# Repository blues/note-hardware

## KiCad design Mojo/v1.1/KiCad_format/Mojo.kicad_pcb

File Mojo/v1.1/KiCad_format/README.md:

# Mojo v1.1 — KiCad format

This directory contains the design files for the Blues **Mojo** v1.1
(internal design name *Mojo-v4*) in **KiCad 9** format. They were generated
by porting the original Altium Designer design files found in
[`../Sources/`](../Sources/), and validated against the shipped BOM and
fabrication outputs — see
[`documentation/Porting-Notes.md`](documentation/Porting-Notes.md) for the
full porting log and [`validation/`](validation/) for the evidence
(ERC/DRC reports, per-layer gerber diffs against the production gerbers,
KiCanvas render checks).

## Contents

| Path | Description |
|---|---|
| `Mojo.kicad_pro` / `Mojo.kicad_prl` | KiCad project (design rules match the Altium DRC report) |
| `Mojo.kicad_sch` | Schematic (single flat sheet, symbols embedded) |
| `Mojo.kicad_pcb` | Board (footprints embedded; zone fills preserved from the Altium import — do not refill) |
| `Mojo.kicad_wks` | Drawing sheet (shared Blues template) |
| `Mojo-altium-import.kicad_sym` / `Mojo-altium-import.pretty/` | Project symbol/footprint libraries captured during the import |
| `sym-lib-table` / `fp-lib-table` | Library tables (project libraries + optional [blues-kicad-lib]) |
| `documentation/` | Porting notes and plotted schematic/board PDFs |
| `manufacturing/Mojo_RevA.zip` | Gerbers + Excellon drill files exported from KiCad (the authoritative production package remains [`../Fabrication/`](../Fabrication/)) |
| `validation/` | Port-QA artifacts: ERC/DRC reports, `<Layer>-{KiCad,Altium,diff}.png` gerber diffs, BOM comparison, KiCanvas screenshots |

The project is self-contained: all symbols and footprints are embedded or
provided in the project libraries. The external [blues-kicad-lib] is only
referenced for consistency with the other Blues KiCad ports and is not
required to open or edit this project. No 3D models are included.

Note: the production ("Normal") assembly variant is represented with KiCad
DNP flags on J2/J3/J7/J8; test point, mounting holes and logo items are
excluded from the BOM, matching the shipped
[`BOM-Mojo-v4-Normal.xls`](../Assembly%20Normal/BOM/).

## Revision History

| Revision | Date | Author | Notes |
|---|---|---|---|
| A | 2026-07-28 | Blues Inc | Initial port of Mojo v1.1 (Mojo-v4) from Altium Designer sources, KiCad 9.0.9 |

### Original (Altium) revision

| Revision | Notes |
|---|---|
| v4 (public v1.1) | Production release, 2024-06 |

[blues-kicad-lib]: https://github.com/blues/blues-kicad-lib

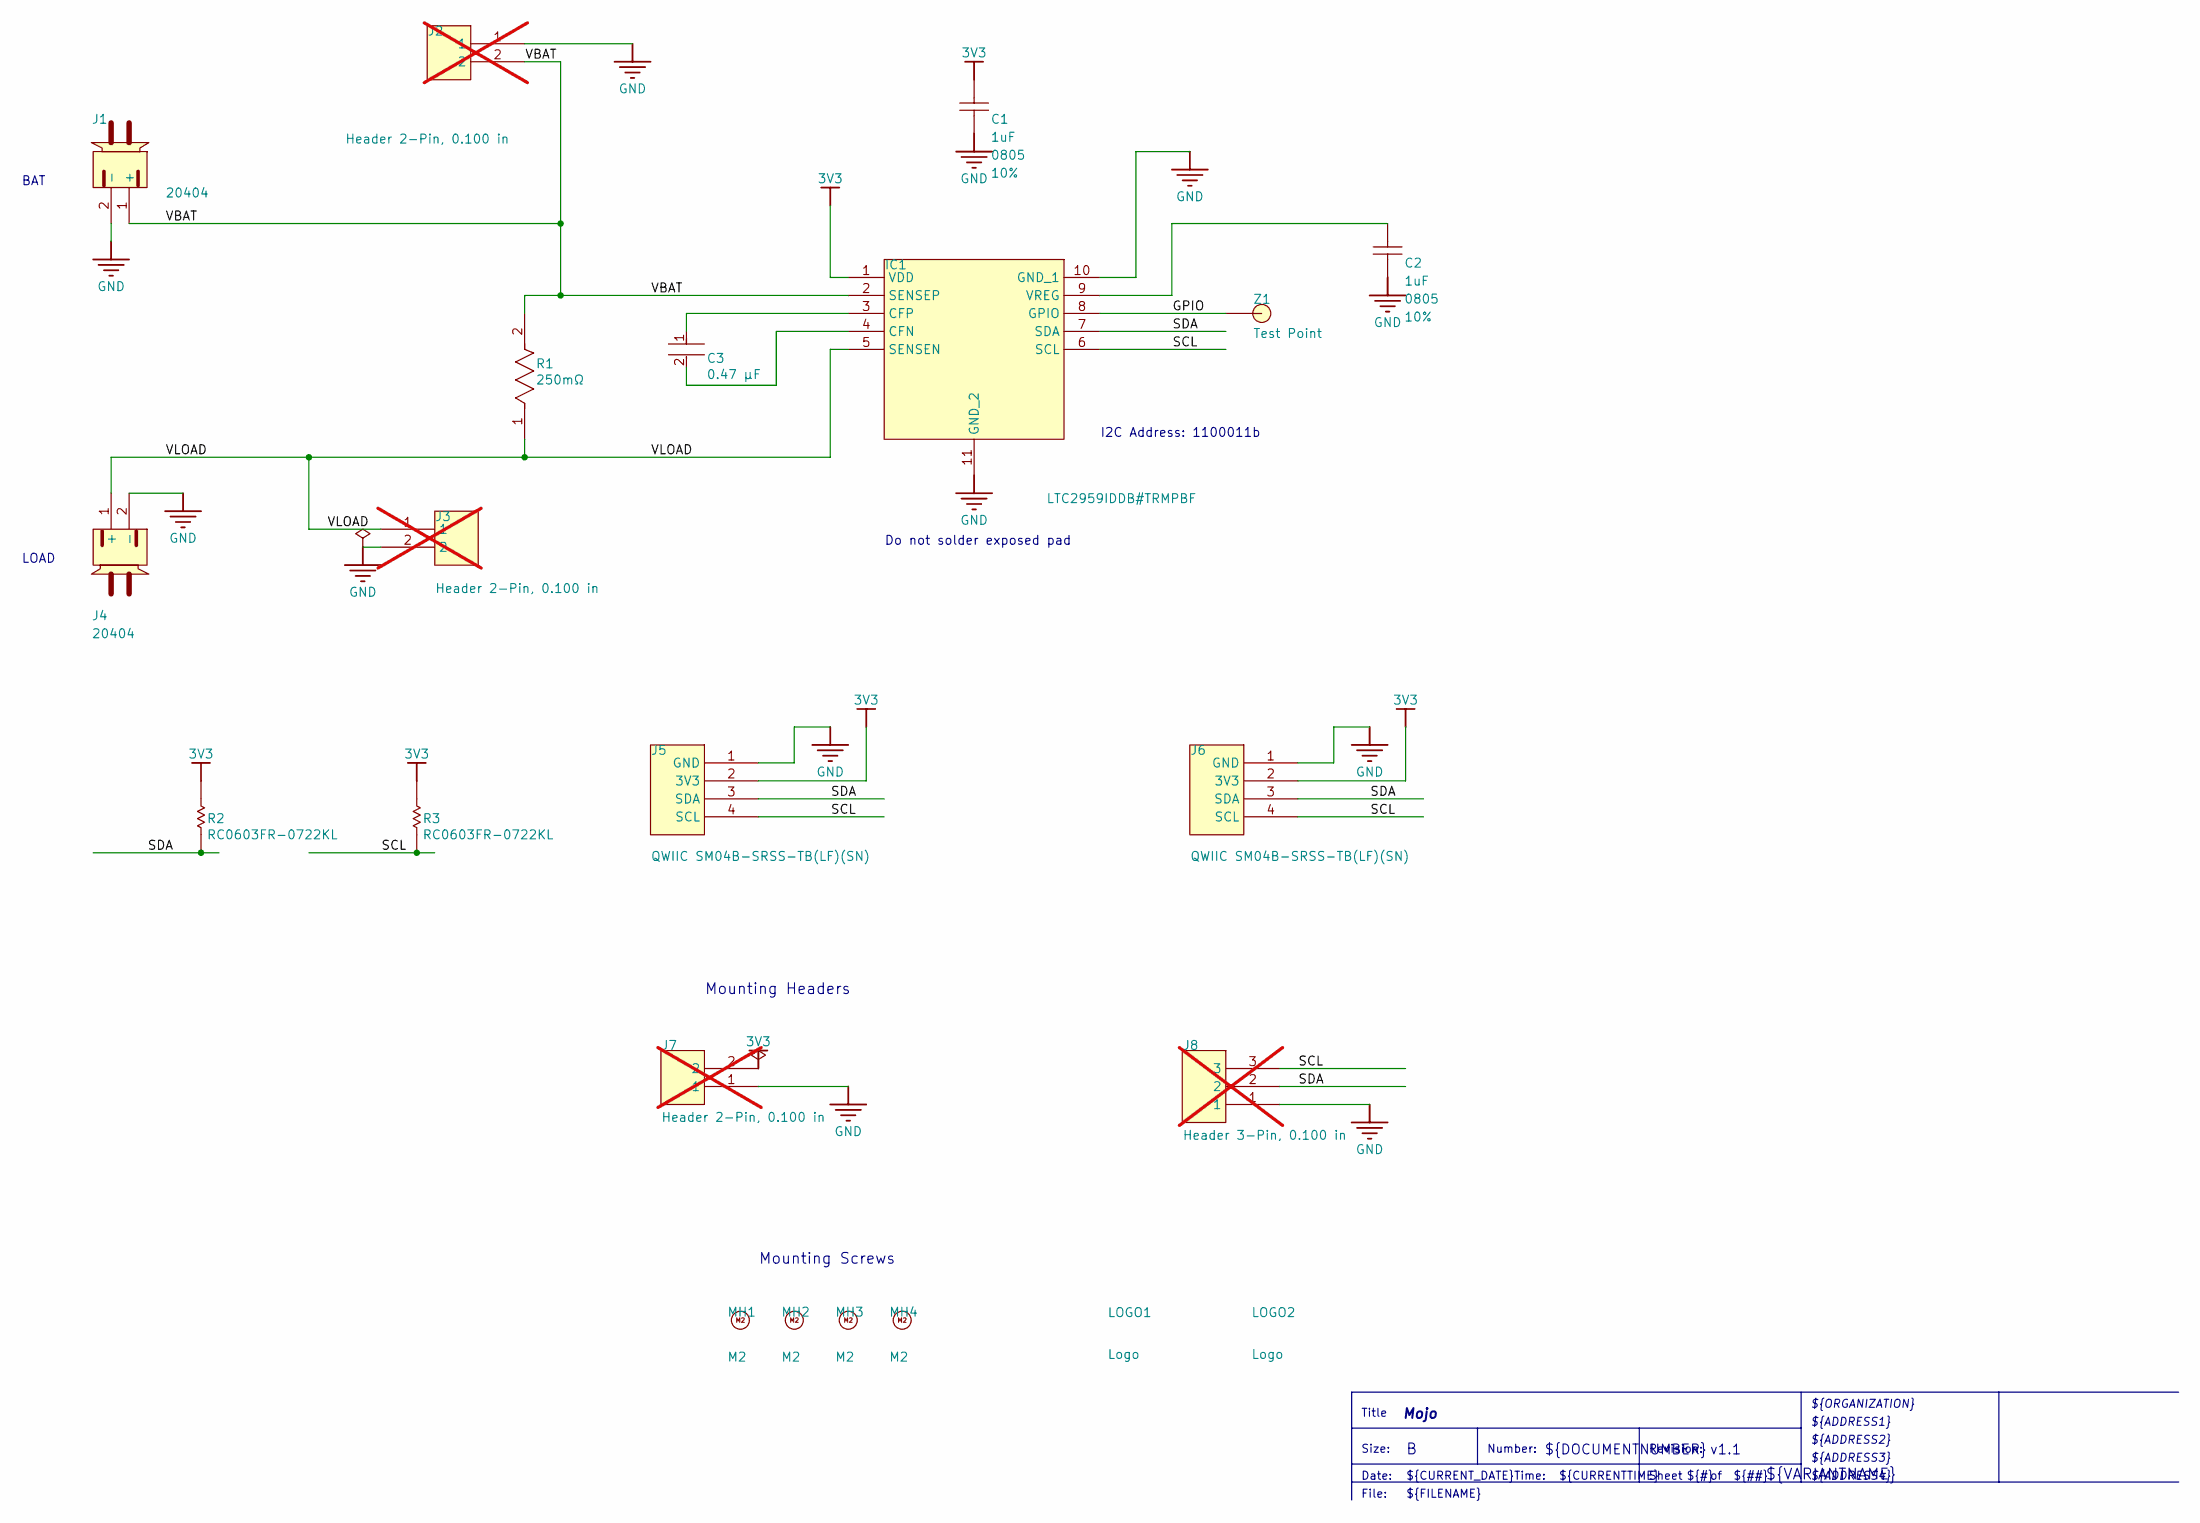
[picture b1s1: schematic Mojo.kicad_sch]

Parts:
C1, C2: GRM216R61E105KA12D; CAPC2013X70X45NL10T25; VOLTAGE 25V; TOLERANCE 10%; PART NUMBER GRM216R61E105KA12D
C3: C0805C474K5RACTU; FP-C0805C-DN-MFG; VOLTAGE RATING 50 V; TOLERANCE 0.1; MANUFACTURER PART NUMBER C0805C474K5RACTU; DIGIKEY DESCRIPTION CAP CER 0.47UF 50V 10% X7R 0805
IC1: LTC2959IDDB#TRMPBF; SON50P200X300X80-11N-D; MANUFACTURER_PART_NUMBER LTC2959IDDB#TRMPBF; MOUSER PART NUMBER 584-LTC2959IDDBTRMPB
J1, J4: 20404; BAT-AF-S2B-PH-SM4; MANUFACTURER PART NUMBER 20404
J2, J3, J7: Header 2-Pin, 0.100 in; HEADER_AA_002; MANUFACTURER PART NUMBER PEC02SAAN; not fitted
J5, J6: QWIIC SM04B-SRSS-TB(LF)(SN); QWIIC_SM04B-SRSS; MAX VOLTAGE RATING (AC) 50V; MAX VOLTAGE RATING (DC) 50V; MANUFACTURER PART NUMBER SM04B-SRSS-TB(LF)(SN)
J8: Header 3-Pin, 0.100 in; HEADER_AA_003; MANUFACTURER PART NUMBER PEC03SAAN; not fitted
LOGO1, LOGO2: Logo
MH1, MH2, MH3, MH4: M2; HOLE_2MM
R1: WSL2010R2500FEA; FP-WSL2010-0_508-MFG; VOLTAGE RATING (DC) 150mV; VOLTAGE RATING (AC) 150mV; MANUFACTURER PART NUMBER WSL2010R2500FEA
R2, R3: RC0603FR-0722KL; RESC1608X55X25LL10T15; TOLERANCE 10%; CURRENT RATING 290 mA
Z1: Test Point; testp_40pad

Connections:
3V3: C1.2, IC1.1 (VDD), J5.2 (3V3), J6.2 (3V3), J7.2, R2.2, R3.2
/GPIO: IC1.8 (GPIO), Z1.1
/SCL: IC1.6 (SCL), J5.4 (SCL), J6.4 (SCL), J8.3, R3.1
/SDA: IC1.7 (SDA), J5.3 (SDA), J6.3 (SDA), J8.2, R2.1
/VBAT: IC1.2 (SENSEP), J1.1 (+), J2.2, R1.2
/VLOAD: IC1.5 (SENSEN), J3.1, J4.1 (+), R1.1
GND: C1.1, C2.1, IC1.10 (GND_1), IC1.11 (GND_2), J1.2 (-), J2.1, J3.2, J4.2 (-), J5.1 (GND), J6.1 (GND), J7.1, J8.1
unnamed: C3.2, IC1.4 (CFN)
unnamed: C3.1, IC1.3 (CFP)
unnamed: C2.2, IC1.9 (VREG)

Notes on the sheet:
I2C Address: 1100011b
Number:
Size:
${CURRENTTIME}
${CURRENT_DATE}
Date:
${#}
${ADDRESS3}
${REVISION}
LOAD
File:
Revision:
BAT
${TITLE}
Mounting Screws
${ADDRESS2}
${VARIANTNAME}
Time:
${##}
Mounting Headers
${ADDRESS1}
Do not solder exposed pad
Title
${DOCUMENTNUMBER}
${ORGANIZATION}
${FILENAME}
${ADDRESS4}
Sheet

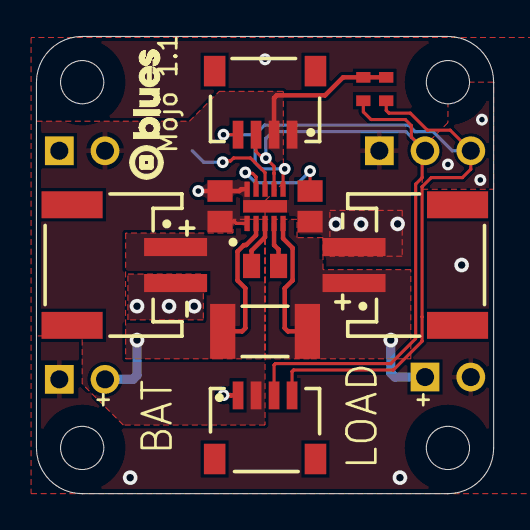
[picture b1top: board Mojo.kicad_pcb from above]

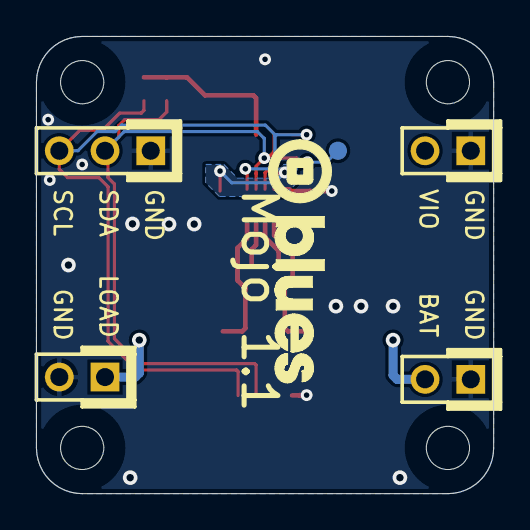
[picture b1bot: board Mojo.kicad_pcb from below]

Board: 2 copper layers, 25.4 x 25.4 mm, 20 parts (5 on the bottom side), 10 nets.

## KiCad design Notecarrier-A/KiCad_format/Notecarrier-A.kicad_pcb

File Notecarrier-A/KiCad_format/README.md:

# Notecarrier-A

This folder contains the design files for the Blues Wireless Notcarrier-A, in KiCad 7 format. They were generated by porting the original OrCad design files. For a detailed description of the porting process, see [PortingNotes](documentation/PortingNotes.md).

**Note:** re-filling zones will result in differences to the `F.Cu` layer. To mimic the unusual clearance near `U5`, the track at (62.9, 109.5) must first be cut to the clipboard, then the zones refilled and then the track pasted back into place. The details are in [PortingNotes](documentation/PortingNotes.md).

Components in this design are sourced from the [blues-kicad-lib](https://github.com/blues/blues-kicad-lib) library. However, with the exception of 3D models, KiCad produces self-contained project files. Thus this project can still be used without access to the library.

## Contents

- This file
 	- `README.md`
- KiCad source files
	- `Notecarrier-A.kicad_dru`
	- `Notecarrier-A.kicad_pcb`	- `Notecarrier-A.kicad_prl`	- `Notecarrier-A.kicad_pro`	- `Notecarrier-A.kicad_sch`	- `Notecarrier-A.kicad_wks`
	- `sym-lib-table`
	- `fp-info-cache`	- `fp-lib-table`
- Documentation	- `documentation/*`
- Manufacturing artefacts
	- `manufacturing/*`
- Design references
	- `reference/*`
- Validation artefacts
	- `validation/*`

## Revision History

| Revision |    Date    |   Author   | Description |
|:--------:| ---------- | ---------- | ----------- |
|     A    | 2023-05-23 | H.Raftery  | Initial port from OrCAD design files, rev 16 (v2.0). |

### Original OrCAD Design File Revision History

| Revision |    Date    |   Author   | Description |
|:--------:| ---------- | ---------- | ----------- |
|    16    | 01/10/2021 | G.Boschini | - Added QWIIC connectors |

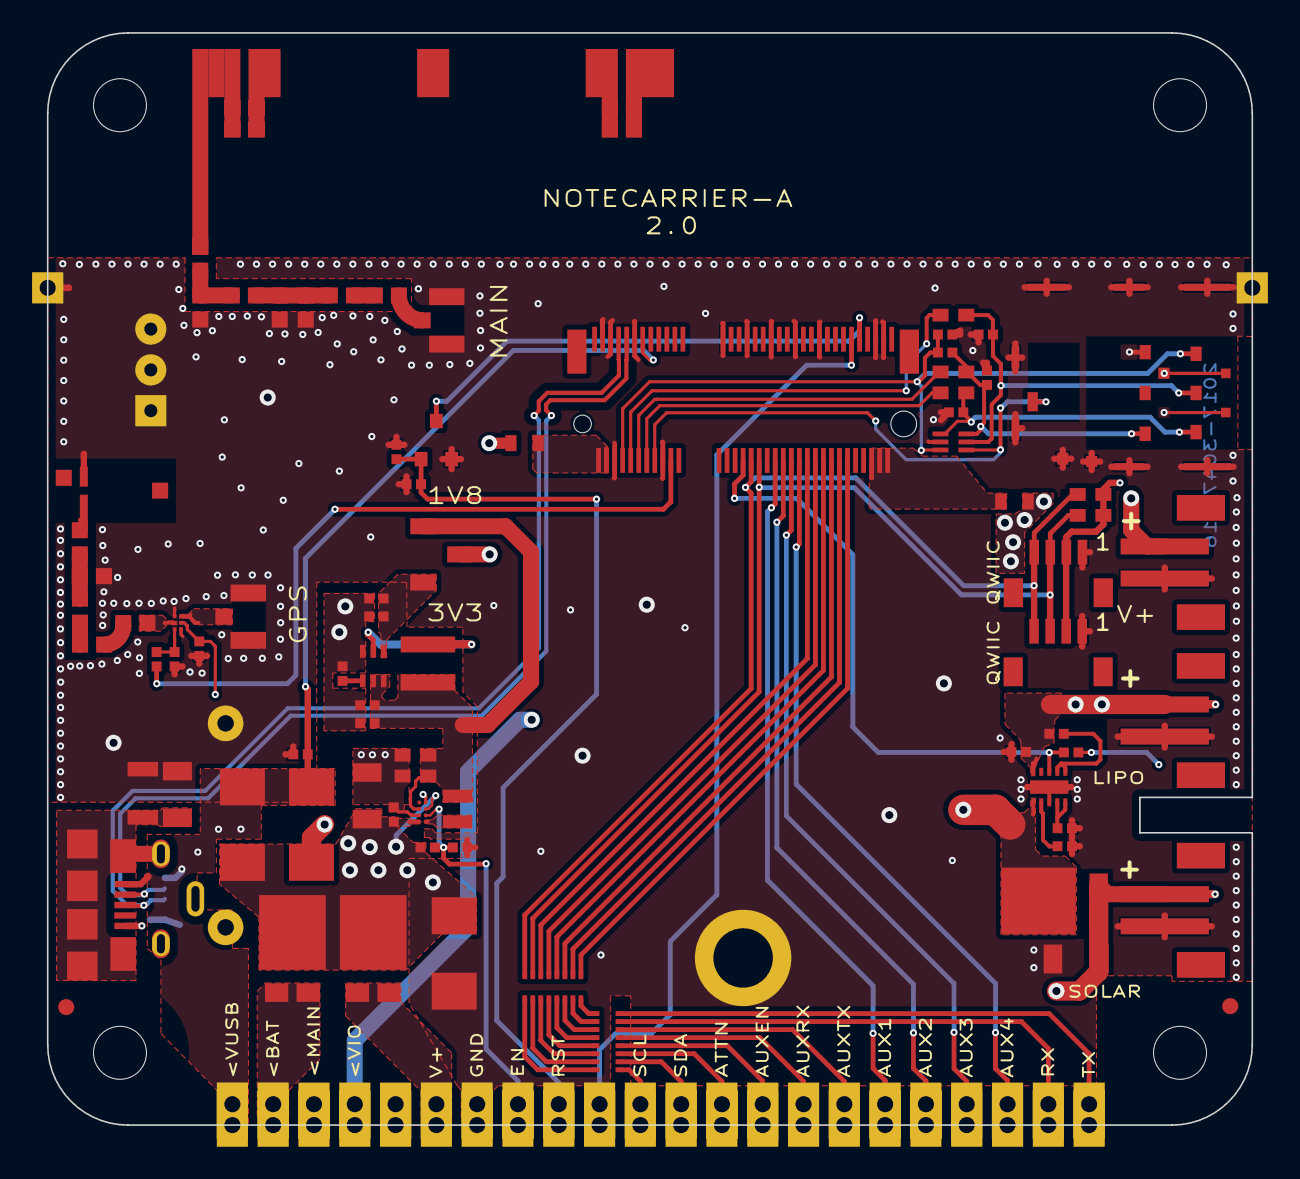
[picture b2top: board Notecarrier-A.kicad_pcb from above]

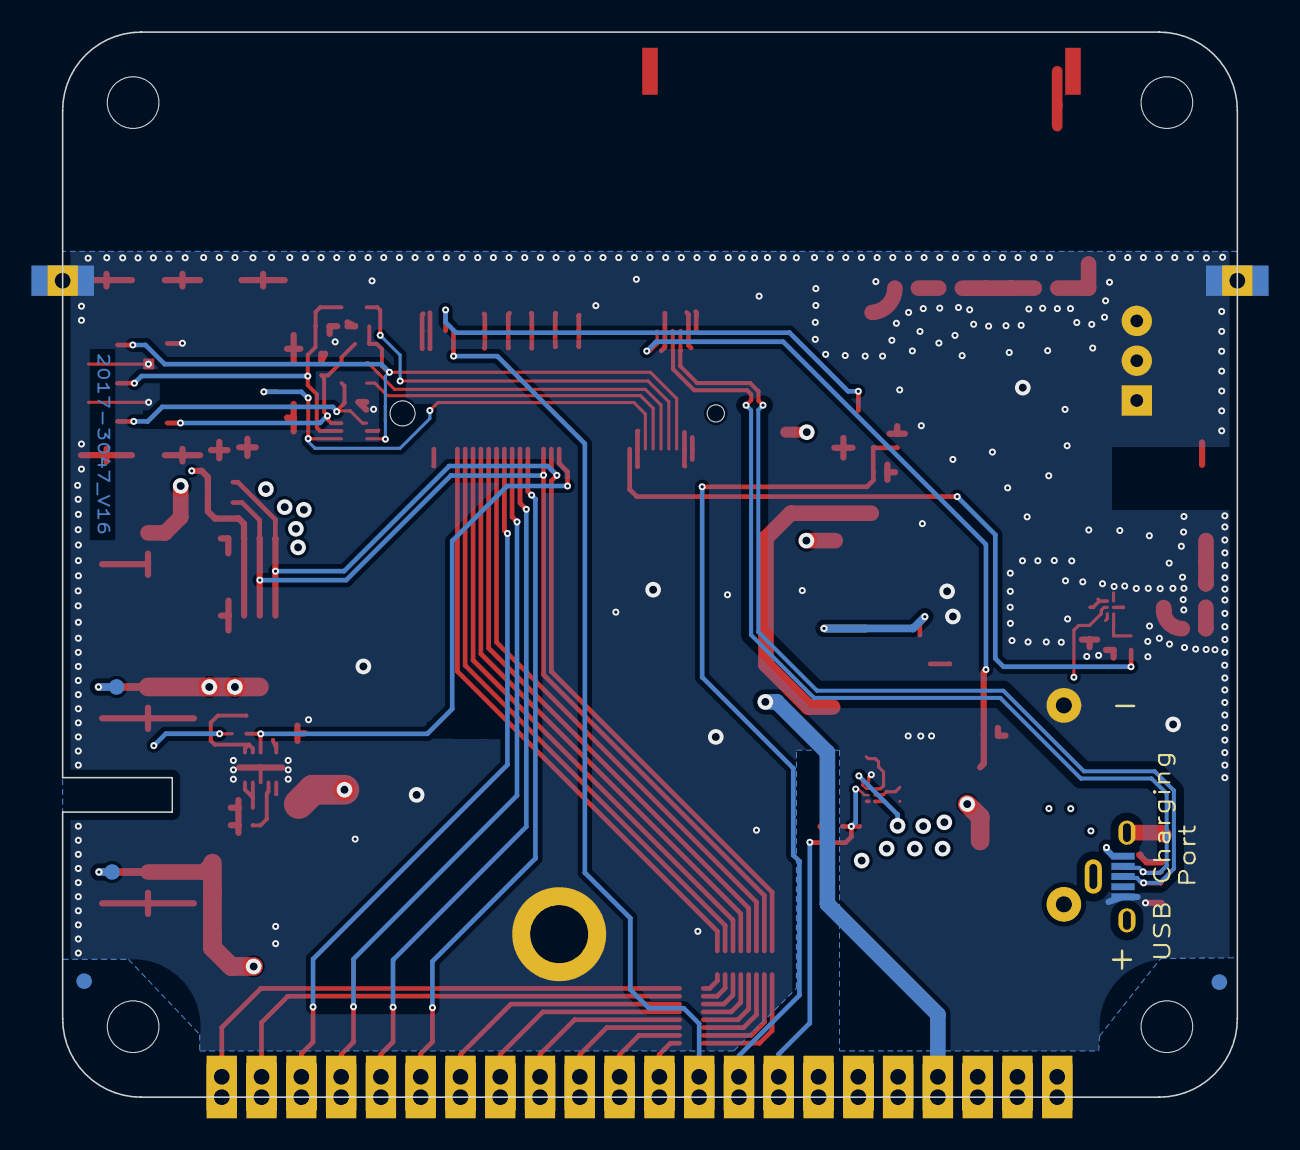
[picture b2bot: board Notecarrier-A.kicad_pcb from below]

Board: 4 copper layers, 75.0 x 68.0 mm, 99 parts (6 on the bottom side), 79 nets.

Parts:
ANT1: NN03-310; ANT-NN03310-LTE_NO-SILK
ANT2: NN03-320; ANT-NN03320-GPS_NO-SILK
BAT1: NU; BATHLD-2464-NO_MECH
C1: 47u/16V-X5R; CS-C-1206
C2: 4.7u/6.3V-X5R; CS-C-0402
C3, C4: 10u/10V-X5R; CS-C-0603
C5, C6, C9, C10, C16, C23: 100n/16V; CS-C-0402
C7, C8: 10u/6.3V-X5R; CS-C-0402
C11: 10n/1kV; CS-C-1206
C12: 10u/25V-X5R; CS-C-1206
C13, C22: 1u/16V-X5R; CS-C-0402
C17, C18, C19: 33p/50V-C0G; CS-C-0402
C21: 1n/50V; FRACTUS-0404_NO-SILK
C25: 0.5p/50V-C0G; FRACTUS-0404_NO-SILK
C26: 1p/50V-C0G; FRACTUS-0404_NO-SILK
C27: 2.2p/50V-C0G; FRACTUS-0404_NO-SILK
C28: 4.6p/50V-C0G; FRACTUS-0404_NO-SILK
C29: 1.1p/50V-C0G; FRACTUS-0404_NO-SILK
DS2, DS3, DS6: FSV1045V; TO277-3
DS4, DS5: STPS3H100U; SMB
F1: SF-0603F150-2; FS-0603
F2: 3.5A/32V; FS-0603
FID1, FID2, FID3, FID4: TPS; FIDUCIAL_MIN-CLEARANCE
H1, H2, H3, H4: MountingHole; FORO-0330-U
J2: NU; J-5-0065-FDS-UUSB1051330001_NO-SILK
J3, J4, J12: B2B-PH-SM4-TBT(LF)(SN); J-2-0200-MDS-B2B-PH-SM4
J5: NanoSIM - SF72S006VBAR2500; J-NANOSIM-SF72S006VBA_NO-FILL
J6: MDT420E01001; J-75-0050-MOS-M2-E_smaller-mask
J7, J8: uFL-R-SMT-1-10; J-3-MDS-UFL_NO-SILK
J9: 12734; J-22-0254-FDT-H0508_EDGE
J10: 00711; J-3-0254-FDT_H0508
J11: 10118192-0002LF; J-5-0065-FOS-USB10118192-NOF
J13, J14: BM04B-SRSS-TBT; J-4-0100-MDS-SH_NO-SILK
L1: XFL4020-222MEC; LS-XFL4020
L2: 1285AS-H-2R2M=P2; LS-0806
L5: LQW15AN7N5H00D; FRACTUS-0404_NO-SILK
L6: LQW18AN12NG80; FRACTUS-0404_NO-SILK
L7: LQW18AN10NG80D; FRACTUS-0404_NO-SILK
L8: LQW18AN8N4G80D; FRACTUS-0404_NO-SILK
L9: LQW15AN2N3G80D; FRACTUS-0404_NO-SILK
OBJ1: 9774025151R; DIST-WASMSIM0250
PAD1, PAD2: TPS; PAD-THT-CAS-0100
Q1: AO3420; SOT23
R1: 10M/5%; RS-0402
R4: 82k; RS-0402
R5: 1M; RS-1206
R6: NU; RS-0402
R8, R10: 10k; RS-0402
R9: 470R; RS-0402
R12, R14, R15: 22R; RS-0603
R16: 15k; RS-0402
R18: 200k; RS-0402
R21: 1k; RS-0402
R22: 100k; RS-0402
R25, R27, R28, R29: 0R; FRACTUS-0404_NO-SILK
R26: NU; FRACTUS-0404_NO-SILK
R30, R31: NU; RS-0603
RR1, RR2: 100R/5%; RR-8X-1506
SW1: CJS-1200TA; SW_CJS-1200TA_NO-SILK
TP4, TP5: TPS; TPS-SPEA
TVS1: SM6T6V8A; SMB
TVS2: ESDLC5V0M5-TP; SOT666_NO-SILK
U1: TPS62748YFPT; XFBGA8
U2: MAX17225ELT; WDFN6-0200X0200
U3: BQ24210DQCT; WSON10-EXP_NO-SILK
U5: BGA725L6E6327FTSA1; XFDFN6_NO-SILK

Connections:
+1V8: C3.1, C4.1, C8.1, C9.1, L1.2, L2.2, SW1.1 (C), U1.C2 (VOS), U2.5 (IN), U2.6 (EN)
+3V3: C6.1, C7.1, SW1.3 (A), U2.1 (OUT)
/Connector/ATTN_P: J6.54 (ATTN_P), RR2.14 (R3_2)
/Connector/AUX_EN_P: J6.56 (AUX_EN_P), RR2.13 (R4_2)
/Connector/AUX_RX_P: J6.58 (AUX_RX_P), RR2.12 (R5_2)
/Connector/AUX_TX_P: J6.60 (AUX_TX_P), RR2.11 (R6_2)
/Connector/GPS_50: J8.1 (In), U5.3 (AO)
/Connector/GPS_50_A: L5.1, U5.5 (AI)
/Connector/GPS_50_B: C21.1, L5.2
/Connector/GPS_50_C: C21.2, R29.1
/Connector/GPS_50_D: C28.1, C29.1, R29.2
/Connector/GPS_50_E: ANT2.4 (FEED-GPS), C29.2
/Connector/LTE_50: J7.1 (In), R28.1
/Connector/LTE_50_A: R27.1, R28.2
/Connector/LTE_50_B: C26.1, C27.2, L7.1, R27.2
/Connector/LTE_50_C: C27.1, L8.1, L9.1
/Connector/LTE_50_D: ANT1.1 (FEED_LTE), L9.2
/Connector/NRST: J6.67 (NRST), Q1.3 (D)
/Connector/RX_P: J6.62 (RX_P), RR2.10 (R7_2)
/Connector/SCL_P: J6.40 (SCL_P), J13.4, J14.4, R31.1, RR2.16 (R1_2)
/Connector/SDA_P: J6.42 (SDA_P), J13.3, J14.3, R30.1, RR2.15 (R2_2)
/Connector/SIM_CLK: J6.14 (SIM_CLK), R14.1
/Connector/SIM_IO: J6.12 (SIM_IO), R12.1
/Connector/SIM_NPRESENT: J5.DSW, J6.16 (SIM_NPRESENT), TVS2.4 (K3)
/Connector/SIM_RST: J6.10 (SIM_RST), R15.1
/Connector/SIM_VCC: C16.1, J5.C1 (VCC), J6.8 (SIM_VCC), R16.2, TVS2.3 (K2)
/Connector/TX_P: J6.64 (TX_P), RR2.9 (R8_2)
/Power/EN: C5.1, J9.8, R1.1, U1.B1 (EN)
ATTN: J9.13, RR1.3 (R3_1)
AUX1: J6.46 (AUX1), J9.17
AUX2: J6.48 (AUX2), J9.18
AUX3: J6.50 (AUX3), J9.19
AUX4: J6.52 (AUX4), J9.20
AUX5: J6.38 (NC38), R6.1, U3.8 (~CHG)
AUX_EN: J9.14, RR1.4 (R4_1)
AUX_RX: J9.15, RR1.5 (R5_1)
AUX_TX: J9.16, RR1.6 (R6_1)
BOOT: J6.65 (NC65), J9.10
GND: ANT2.2 (M2), BAT1.2 (-), C1.2, C2.2, C3.2, C4.2, C5.2, C6.2, C7.2, C8.2, C9.2, C10.2, C11.2, C12.2, C13.2, C16.2, C17.2, C18.2, C19.2, C22.2, C23.2, C26.2, C28.2, J2.5 (GND), J3.2, J4.2, J5.C5 (GND), J5.CSW, J5.SH, J6.3 (GND), J6.5 (GND), J6.6 (GND), J6.11 (GND), J6.18 (GND), J6.33 (GND), J6.39 (GND), J6.45 (GND), J6.51 (GND), J6.57 (GND), J6.71 (GND), J6.73 (GND), J7.2 (Ext), J8.2 (Ext), J9.7, J10.1, J10.2, J10.3, J11.5 (GND), J12.2, J13.1, J14.1, L7.2, L8.2, OBJ1.1, PAD1.1, PAD2.1, Q1.2 (S), R4.1, R5.2, R9.1, R10.1, R21.1, R22.1, TVS1.2 (A2), TVS2.2 (A), U1.B2 (GND), U1.D1 (CTRL), U2.3 (GND), U3.3 (VSS), U3.11 (EXP), U5.1 (GND), U5.4 (GNDRF)
unnamed: DS5.1 (K), DS6.3 (C), U3.1 (VBUS)
unnamed: C11.1, J2.6 (Shield), J11.6 (Shield), R5.1
unnamed: ANT1.2 (MN1-A), C25.2, L6.1
unnamed: ANT1.3 (MN1-B), C25.1, L6.2
unnamed: ANT1.5 (MN2-A), R25.1, R26.1
unnamed: ANT1.6 (MN2-B), R25.2, R26.2
unnamed: C18.1, J5.C3 (CLK), R14.2, TVS2.1 (K1)
unnamed: C19.1, J5.C7 (I/O), R12.2, R16.1, TVS2.6 (K5)
unnamed: C17.1, J5.C2 (RST), R15.2, TVS2.5 (K4)
unnamed: RR1.16 (R1_2), RR2.1 (R1_1)
unnamed: RR1.15 (R2_2), RR2.2 (R2_1)
unnamed: RR1.14 (R3_2), RR2.3 (R3_1)
unnamed: RR1.13 (R4_2), RR2.4 (R4_1)
unnamed: RR1.12 (R5_2), RR2.5 (R5_1)
unnamed: RR1.11 (R6_2), RR2.6 (R6_1)
unnamed: RR1.10 (R7_2), RR2.7 (R7_1)
unnamed: RR1.9 (R8_2), RR2.8 (R8_1)
unnamed: L2.1, U1.A1 (SW)
unnamed: L1.1, U2.2 (LX)
unnamed: R4.2, U2.4 (SEL)
unnamed: R9.2, U3.2 (ISET)
unnamed: R10.2, U3.4 (VTSB), U3.5 (TS)
unnamed: R8.1, U3.6 (~PG), U3.7 (~EN)
unnamed: R18.1, R22.2, U5.6 (PON)
RST: C23.1, J9.9, Q1.1 (G), R21.2
RX: J9.21, RR1.7 (R7_1)
SCL: J9.11, RR1.1 (R1_1)
SDA: J9.12, RR1.2 (R2_1)
TX: J9.22, RR1.8 (R8_1)
USB_DM: J2.2 (D-), J6.9 (USB_DM), J11.2 (D-)
USB_DP: J2.3 (D+), J6.7 (USB_DP), J11.3 (D+)
V+: DS2.1 (A1), DS2.2 (A2), J9.6, J12.1
VACT_GPS_OUT: J6.20 (VACT_GPS_OUT), R18.2
VBAT: BAT1.1 (+), C13.1, DS3.1 (A1), DS3.2 (A2), J4.1, J9.2, R8.2, TP4.1, U3.10 (BAT)
VIO: C22.1, F1.1, J9.4, J13.2, J14.2, R6.2, R30.2, R31.2, SW1.2 (B), U5.2 (VCC)
VIO_P: F1.2, J6.2 (VIO_P), J6.4 (VIO_P)
VMAIN: C1.1, C2.1, DS2.3 (C), DS3.3 (C), DS4.1 (K), F2.1, J9.3, R1.2, TVS1.1 (A1), U1.A2 (VIN), U1.C1 (VSEL)
VMODEM_P: F2.2, J6.70 (VMODEM_P), J6.72 (VMODEM_P), J6.74 (VMODEM_P)
VSOLAR: C12.1, DS6.1 (A1), DS6.2 (A2), J3.1, J9.5, TP5.1
VUSB: C10.1, DS4.2 (A), DS5.2 (A), J2.1 (VBUS), J6.13 (VUSB), J9.1, J11.1 (VBUS)

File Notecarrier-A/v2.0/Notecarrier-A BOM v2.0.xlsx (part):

PROJECT |  | 2017-3047 (NOTECARRIER-M2-AL) |  | Blues Inc
REVISION |  | 16
SCHEMATIC |  | 20173047_NOTECARRIER-M2-AL_V16
DATE |  | 15/11/2021
Item | Quantity | Reference | Part | MPN | Description | Temperature | Type | Package
1 | 1 | ANT1 | NN03-310 | NN03-310 | ANTENNA CHIP LTE/GNSS/BT D=30X3X1 NN03-310 IGNION SMT | -40°..+125° | SMD | ANT-NN03310-LTE
2 | 1 | ANT2 | NN03-320 | NN03-320 | ANTENNA CHIP GPS/BT D=3X7X2 NN03-320 IGNION SMT | -40°..+85° | SMD | ANT-NN03320-GPS
3 | 1 | CS1 | CS V16 4L 35um |  | C.S. NOTECARRIER-M2-AX V16 (75X65)mm 4L/SO/SR ENIG TG150 sp=1.6mm Cu=35um (CONT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 | TG150
4 | 1 | C1 | 47u/16V-X5R | C3216X5R1E476M160AC | CHIP CAP.CER. 47uF 16V 20% X5R 1206 |  | SMD | CS-C-1206
5 | 1 | C2 | 4.7u/6.3V-X5R | JMK105BBJ475MV-F | CHIP CAP.CER. 4.7uF 6.3V 20% X5R 0402 |  | SMD | CS-C-0402
6 | 2 | C3,C4 | 10u/10V-X5R | GRM188R61A106KE69D | CHIP CAP.CER. 10uF 10V 10% X5R 0603 |  | SMD | CS-C-0603
7 | 6 | C5,C6,C9,C10,C16,C23 | 100n/16V | CC0402KRX7R7BB104 | CHIP CAP.CER. 100nF 16V 10% X7R 0402 |  | SMD | CS-C-0402
8 | 2 | C7,C8 | 10u/6.3V-X5R | GRM155R60J106ME44D | CHIP CAP.CER. 10uF 6.3V 20% X5R 0402 | -55°..+85° | SMD | CS-C-0402
9 | 1 | C11 | 10n/1kV | C1206C103KDRACTU | CHIP CAP.CER. 10nF 1000V 10% X7R 1206 |  | SMD | CS-C-1206
10 | 1 | C12 | 10u/25V-X5R | CL31A106KAHNNNE | CHIP CAP.CER. 10uF 25V X5R 10% 1206 |  | SMD | CS-C-1206
11 | 2 | C13,C22 | 1u/16V-X5R | EMK105BJ105MVHF | CHIP CAP.CER. 1uF 16V 10% X5R 0402 |  | SMD | CS-C-0402
12 | 3 | C17,C18,C19 | 33p/50V-C0G | CC0402JRNPO9BN330 | CHIP CAP.CER. 33pF 50V 5% C0G 0402 |  | SMD | CS-C-0402
13 | 1 | C21 | 1n/50V | C0402C102K5RECAUTO | CHIP CAP.CER. 1nF 50V 10% X7R 0402 |  | SMD | FRACTUS-0404
14 | 1 | C25 | 0.5p/50V-C0G | GJM1555C1HR50WB01 | CHIP CAP.CER. 0.5pF 50V ±0.05pF C0G 0603 GJM1555C1HR50WB01 MURATA | -55°..+125° | SMD | FRACTUS-0404
15 | 1 | C26 | 1p/50V-C0G | GJM1555C1H1R0WB01 | CHIP CAP.CER. 1pF 50V ±0.05pF C0G 0603 GJM1555C1H1R0WB01 MURATA | -55°..+125° | SMD | FRACTUS-0404
16 | 1 | C27 | 2.2p/50V-C0G | GJM1555C1H2R2WB01 | CHIP CAP.CER. 2.2pF 50V ±0.05pF C0G 0603 GJM1555C1H2R2WB01 MURATA | -55°..+125° | SMD | FRACTUS-0404
17 | 1 | C28 | 4.6p/50V-C0G | GJM1555C1H4R6WB01D | CHIP CAP.CER. 4.6pF 50V ±0.05pF C0G 0402 GJM1555C1H4R6WB01D MURATA | -55°..+125° | SMD | FRACTUS-0404
18 | 1 | C29 | 1.1p/50V-C0G | GJM1555C1H1R1WB01D | CHIP CAP.CER. 1.1pF 50V ±0.05pF C0G 0402 GJM1555C1H1R1WB01D MURATA | -55°..+125° | SMD | FRACTUS-0404
19 | 3 | DS2,DS3,DS6 | FSV1045V | FSV1045V | SCHOTTKY DIODE 10A 45V FSV1045V TO277-3 SMT | -55°..+150° | SMD | TO277-3
20 | 2 | DS4,DS5 | STPS3H100U | STPS3H100U | SCHOTTKY DIODE 3A 100V STPS3H100U SMB SMT |  | SMD | SMB
21 | 1 | F1 | SF-0603F150-2 | SF-0603F150-2 | RAPID FUSE 1.5A 32V 0603 SF-0603F150-2 BOURNS SMT | -40°..+105° | SMD | FS-0603
22 | 1 | F2 | 3.5A/32V | 0603SFV350F/32-2 | RAPID FUSE 3.5A 32V 0603 0603SFV350F/32-2 LITTELFUSE SMT | -55°..+125° | SMD | FS-0603
23 | 3 | J3,J4,J12 | B2B-PH-SM4-TBT(LF)(SN) | B2B-PH-SM4-TBT(LF)(SN) | CONN. PH 2P M/D P=2 B2B-PH-SM4-TBT(LF)(SN) JST SMT | -25°..+85° | SMD | J-2-0200-MDS-B2B-PH-SM4
24 | 1 | J5 | NanoSIM - SF72S006VBAR2500 | SF72S006VBAR2500 | CONN. NANOSIM 8P F/90° PUSH-PUSH SF72S006VBAR2500 JAE ELECTRONICS SMT | -25°..+85° | SMD | J-NANOSIM-SF72S006VBA
25 | 1 | J6 | MDT420E01001 | MDT420E01001 | CONN. M.2 75P M/90° P=0.5 MDT420E01001 AMPHENOL SMT | -40°..+80° | SMD | J-75-0050-MOS-M2-E
26 | 2 | J7,J8 | uFL-R-SMT-1-10 | U.FL-R-SMT-1(10) | CONN. RF M U.FL-R-SMT-1(10) HIROSE SMT | -40°..+90° | SMD | J-3-MDS-UFL
27 | 1 | J9 | 12734 | 12734 | STRIP 22P F/D P=2.54 H=5.08 12734 4UCON | -55..+105 | THT | J-22-0254-FDT-H0508_EDGE
28 | 1 | J10 | 00711 | 00711 | STRIP 3P F/D P=2.54 H=5.08 00711 4UCON | -55..+105 | THT | J-3-0254-FDT-H0508
29 | 1 | J11 | 10118192-0002LF | 10118192-0002LF | CONN. USB F/90° TIPO MICRO-B C.S. 10118192-0002LF FCI SMT | -30°..+80° | SMD | J-5-0065-FOS-USB10118192-NOF
30 | 2 | J13,J14 | BM04B-SRSS-TBT | BM04B-SRSS-TBT(LF)(SN) | CONN. SH 4P M/D P=1 BM04B-SRSS-TBT(LF)(SN) JST SMT | -25°..+85° | SMD | J-4-0100-MDS-SH
31 | 1 | L1 | XFL4020-222MEC | XFL4020-222MEC | INDUCTOR 2.2 uH 3.1A 20% XFL4020-222MEC COILCRAFT SMT | -40°..+125° | SMD | LS-XFL4020
32 | 1 | L2 | 1285AS-H-2R2M=P2 | 1285AS-H-2R2M=P2 | INDUCTOR 2.2uH 1.5A 20% 0806 1285AS-H-2R2M=P2 MURATA SMT | -40°..+85° | SMD | LS-0806
33 | 1 | L5 | LQW15AN7N5H00D | LQW15AN7N5H00D | INDUCTOR 7.5nH 0.57A 3% A FILO 0402 LQW15AN7N5H00D MURATA SMT | -55°..+125° | SMD | FRACTUS-0404
34 | 1 | L6 | LQW18AN12NG80 | LQW18AN12NG80 | INDUCTOR 12nH 1.5A 2% 0603 LQW18AN12NG80 MURATA SMT | -55°..+125° | SMD | FRACTUS-0404
35 | 1 | L7 | LQW18AN10NG80D | LQW18AN10NG80D | INDUCTOR 10nH 1.6A 2% 0603 LQW18AN10NG80D MURATA SMT | -55°..+125° | SMD | FRACTUS-0404
36 | 1 | L8 | LQW18AN8N4G80D | LQW18AN8N4G80D | INDUCTOR 8.4nH 1.6A 2% 0603 LQW18AN8N4G80D MURATA SMT | -55°..+125° | SMD | FRACTUS-0404
37 | 1 | L9 | LQW15AN2N3G80D | LQW15AN2N3G80D | INDUCTOR 2.3nH 2.53A 2% 0402 LQW15AN2N3G80D MURATA SMT | -55°..+125° | SMD | FRACTUS-0404
38 | 1 | OBJ1 | 9774025151R | 9774025151R | STEEL SPACER 5.1X2.5 9774025151R W.E SMT |  | FAE | SMD
39 | 1 | Q1 | AO3420 | AO3420 | TRANSISTOR MOSFET N AO3420 SOT-23 ALPHA-OMEGA SMT | -55°..+150° | SMD | SOT23
40 | 2 | RR1,RR2 | 100R/5% | CAY16-101J8LF | ARRAY CHIP RES. 8R sing. 100R 5% 1506 CAY16-101J8LF BOURNS SMT | -55°..+125° | SMD | RR-8X-1506
41 | 1 | R1 | 10M/5% | SG73S1ETTP106J | CHIP RES. 10M 0402 1/8W 5% | -55°..+125° | SMD | RS-0402
42 | 1 | R4 | 82k | CRCW040282K0FKTDBC | CHIP RES. 82K 0402 1/16W 1% | -55°..+155° | SMD | RS-0402
43 | 1 | R5 | 1M | CRCW12061M00FKTABC | CHIP RES. 1M 1206 1/4W 1% |  | SMD | RS-1206
44 | 2 | R8,R10 | 10k | RC0402FR-0710KL | CHIP RES. 10K 0402 1/16W 1% | -55°..+125° | SMD | RS-0402
45 | 1 | R9 | 470R | CRCW0402470RFKTDBC | CHIP RES. 470R 0402 1/16W 1% |  | SMD | RS-0402
46 | 3 | R12,R14,R15 | 22R | RC0603FR-0722RL | CHIP RES. 22R 0603 1/16W 1% |  | SMD | RS-0603
47 | 1 | R16 | 15k | RC0402FR-0715KL | CHIP RES. 15K 0402 1/16W 1% | -55°..+155° | SMD | RS-0402
48 | 1 | R18 | 200k | RC0402FR-07200KL | CHIP RES. 200K 0402 1/16W 1% |  | SMD | RS-0402
49 | 1 | R21 | 1k | RC0402FR-071KL | CHIP RES. 1K 0402 1/16W 1% | -55°..+155° | SMD | RS-0402
50 | 1 | R22 | 100k | RC0402FR-07100KL | CHIP RES. 100K 0402 1/16W 1% |  | SMD | RS-0402
51 | 4 | R25,R27,R28,R29 | 0R | RC0603JR-070RL | CHIP RES. 0R 0603 1/16W 1% | -55°..+150° | SMD | FRACTUS-0404
52 | 1 | SW1 | CJS-1200TA | CJS-1200TA | SWITCH SLIDE ON-ON DA C.S. CJS-1200TA NIDEC COPAL ELECTRONICS SMT | -40°..+85° | SMD | SW-CJS1200TA
53 | 1 | TVS1 | SM6T6V8A | SM6T6V8A | DIODE TVS TRANSIL UNIDIR. 600W 6.8V SM6T6V8A SMB SMT |  | SMD | SMB
54 | 1 | TVS2 | ESDLC5V0M5-TP | ESDLC5V0M5-TP | DIODE TVS TRANSIL UNIDIR. 20W 5V ESDLC5V0M5-TP SOT563 SMT | -65°..+150° | SMD | SOT666
55 | 1 | U1 | TPS62748YFPT | TPS62748YFPT | I.C. TPS62748YFPT TEXAS DSBGA8 SMT | -40°..+85° | SMD | XFBGA8
56 | 1 | U2 | MAX17225ELT | MAX17225ELT+T | I.C. MAX17225ELT+T MAXIM W-DFN6 SMT | -40°..+85° | SMD | WDFN6-0200X0200
57 | 1 | U3 | BQ24210DQCT | BQ24210DQCT | I.C. BQ24210DQCT WSON10 TEXAS SMT | -40°..+85° | SMD | WSON10-EXP
58 | 1 | U5 | BGA725L6E6327FTSA1 | BGA725L6E6327FTSA1 | I.C. BGA725L6E6327FTSA1 INFINEON TSLP-6 SMT | -40°..+125° | SMD | XFDFN6
 | 82
MECHANICAL
1 | 1 | ASS1 | PHILIPS SCREW | 179-5691 | SCREW TCEI 2.5X4 INOX DIN 7985 PHILIPS
2 | 2 | ASS2,ASS3 | uFL 50mm | 415-0086-050 | COAX CABLE uFl-uFl 415-0086-050 HIROSE CINCH CONNECTIVITY SOLUTIONS JOHNSON
3 | 1 |  |  | MGKWKB500M | PINK ANTISTATIC ESD BAG 76X130mm MGKWKB500M
4 | 1 |  |  |  | BLUES LABEL
NOT MOUNTED
1 | 1 | BAT1 | NU | 2464 | BATTERY HOLDER 2464 KEYSTONE |  | THT | BATHLD-2464-NO_MECH
2 | 4 | FID1,FID2,FID3,FID4 | TPS |  | FIDUCIAL |  | SMD | FIDUCIAL
3 | 1 | J2 | NU | 1051330001 | CONN. USB F/D TIPO MICRO-B C.S. 1051330001 MOLEX SMT | -30°..+85° | SMD | J-5-0065-FDS-UUSB1051330001
4 | 2 | PAD1,PAD2 | TPS |  | CASTELLATED EDGE VIAS |  | THT | PAD-THT-CAS-0100
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

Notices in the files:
Notecarrier-A/KiCad_format/Notecarrier-A.kicad_pcb:
Blues Inc (Copyright (c) 2023 Blues Inc)
